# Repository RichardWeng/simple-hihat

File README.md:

# simple-hihat
 Simple eurorack hihat module

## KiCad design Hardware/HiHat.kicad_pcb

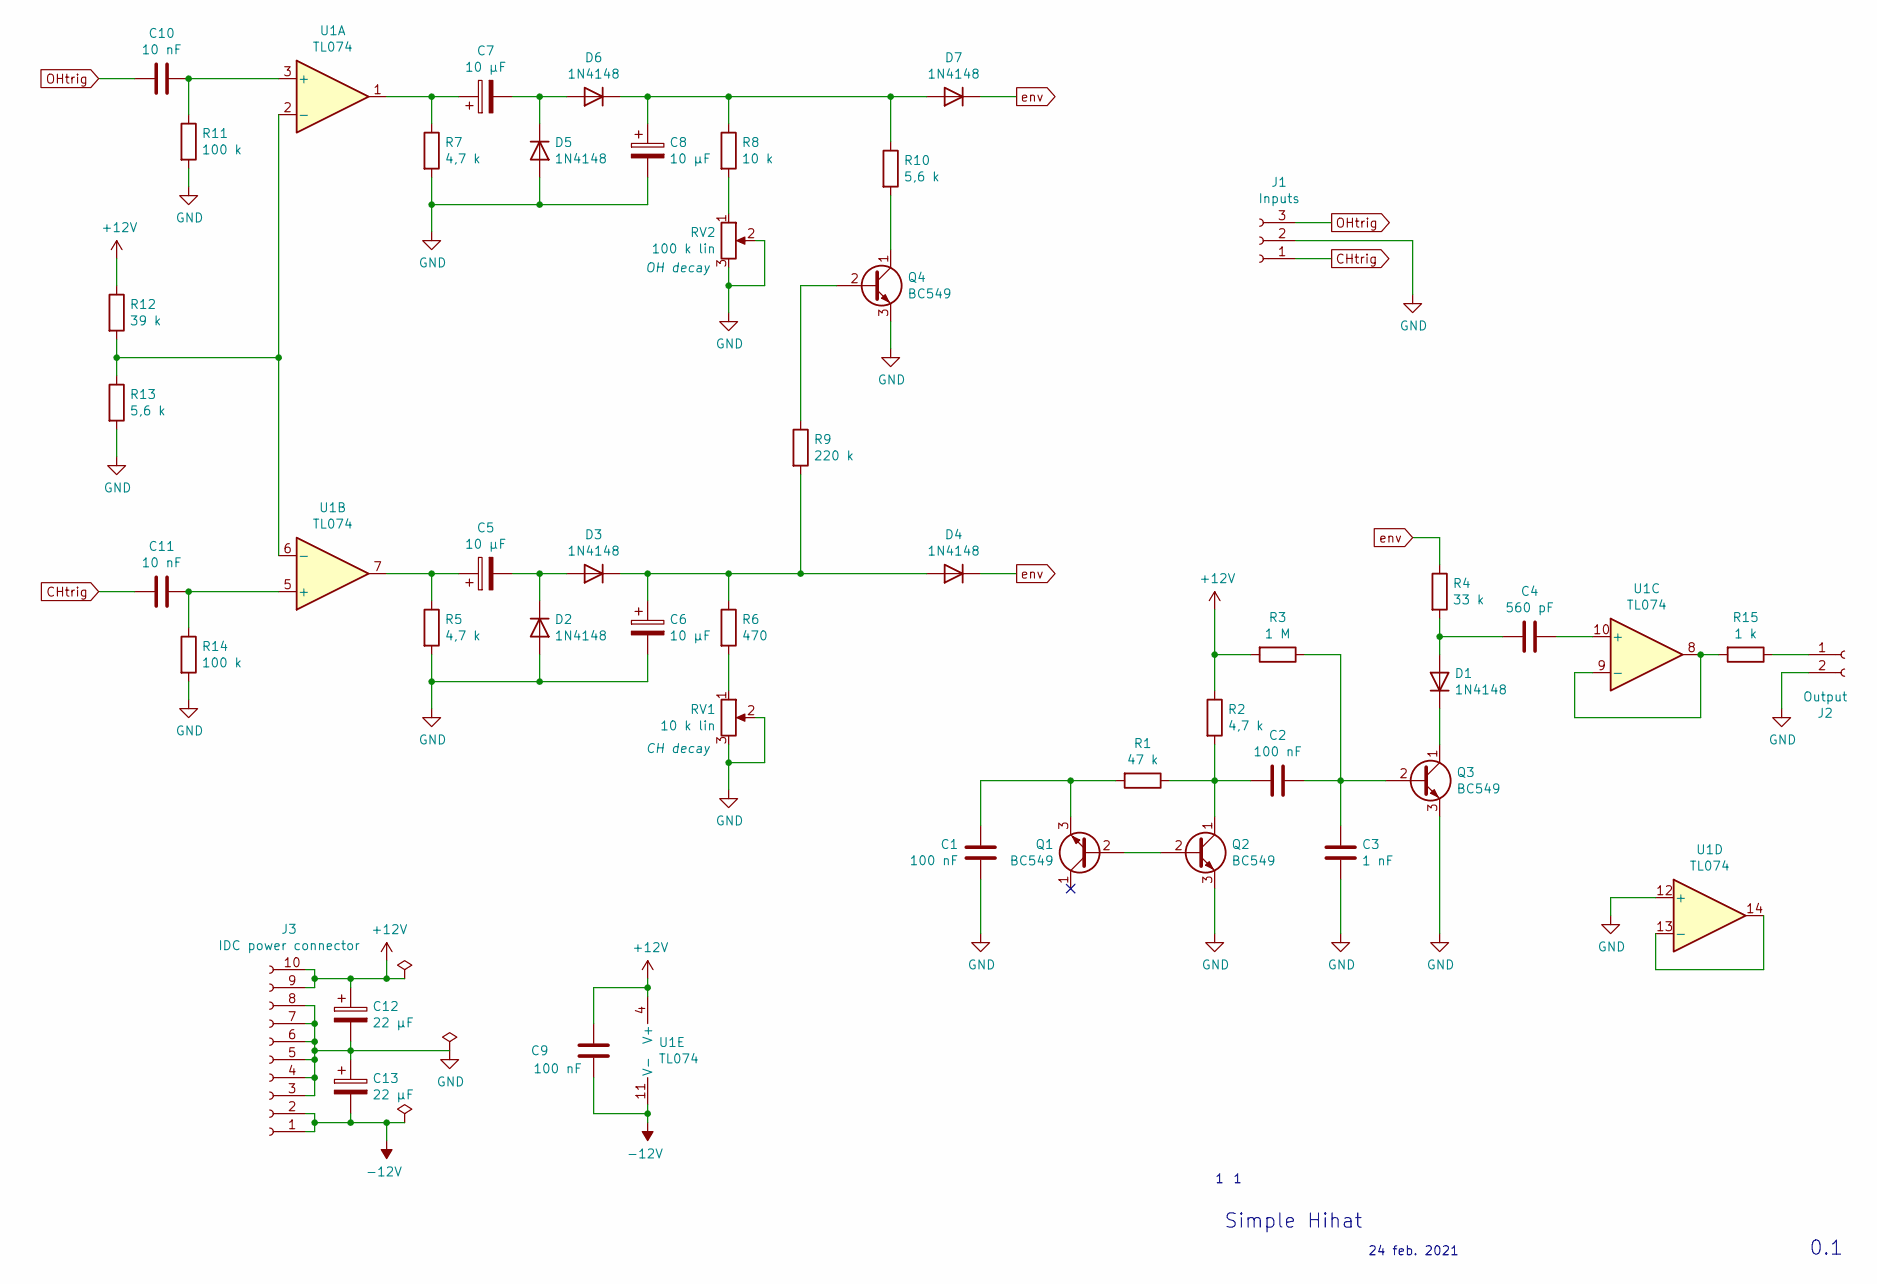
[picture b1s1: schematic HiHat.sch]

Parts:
C1, C2: 100 nF; C_Rect_L7.2mm_W5.5mm_P5.00mm_FKS2_FKP2_MKS2_MKP2
C3: 1 nF; C_Rect_L7.2mm_W2.5mm_P5.00mm_FKS2_FKP2_MKS2_MKP2
C4: 560 pF; C_Disc_D4.3mm_W1.9mm_P5.00mm
C5, C6, C7, C8: 10 µF; CP_Radial_D6.3mm_P2.50mm
C9: 100 nF; C_Rect_L7.2mm_W2.5mm_P5.00mm_FKS2_FKP2_MKS2_MKP2
C10, C11: 10 nF; C_Rect_L7.2mm_W5.5mm_P5.00mm_FKS2_FKP2_MKS2_MKP2
C12, C13: 22 µF; CP_Radial_D6.3mm_P2.50mm
D1, D2, D3, D4, D5, D6, D7: 1N4148; D_DO-35_SOD27_P10.16mm_Horizontal
J1: Inputs; JST_EH_B3B-EH-A_1x03_P2.50mm_Vertical
J2: Output; JST_EH_B2B-EH-A_1x02_P2.50mm_Vertical
J3: IDC power connector; IDC-Header_2x05_P2.54mm_Vertical
Q1, Q2, Q3, Q4: BC549; TO-92_Inline_Wide
R1: 47 k; R_Axial_DIN0207_L6.3mm_D2.5mm_P10.16mm_Horizontal
R2, R5, R7: 4,7 k; R_Axial_DIN0207_L6.3mm_D2.5mm_P10.16mm_Horizontal
R3: 1 M; R_Axial_DIN0207_L6.3mm_D2.5mm_P10.16mm_Horizontal
R4: 33 k; R_Axial_DIN0207_L6.3mm_D2.5mm_P10.16mm_Horizontal
R6: 470; R_Axial_DIN0207_L6.3mm_D2.5mm_P10.16mm_Horizontal
R8: 10 k; R_Axial_DIN0207_L6.3mm_D2.5mm_P10.16mm_Horizontal
R9: 220 k; R_Axial_DIN0207_L6.3mm_D2.5mm_P10.16mm_Horizontal
R10, R13: 5,6 k; R_Axial_DIN0207_L6.3mm_D2.5mm_P10.16mm_Horizontal
R11, R14: 100 k; R_Axial_DIN0207_L6.3mm_D2.5mm_P10.16mm_Horizontal
R12: 39 k; R_Axial_DIN0207_L6.3mm_D2.5mm_P10.16mm_Horizontal
R15: 1 k; R_Axial_DIN0207_L6.3mm_D2.5mm_P10.16mm_Horizontal
RV1: 10 k lin; Potentiometer_Alps_RK09Y11_Single_Horizontal
RV2: 100 k lin; Potentiometer_Alps_RK09Y11_Single_Horizontal
U1: TL074; DIP-14_W7.62mm_Socket_LongPads

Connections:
+12V: C9.1, C12.1, J3.9, J3.10, R2.1, R3.2, R12.1, U1.4 (V+)
-12V: C9.2, C13.2, J3.1, J3.2, U1.11 (V-)
CHtrig: C11.2, J1.1
GND: C1.2, C3.2, C6.2, C8.2, C12.2, C13.1, D2.2 (A), D5.2 (A), J1.2, J2.2, J3.3, J3.4, J3.5, J3.6, J3.7, J3.8, Q2.3 (E), Q3.3 (E), Q4.3 (E), R5.2, R7.2, R11.2, R13.2, R14.2, RV1.2, RV1.3, RV2.2, RV2.3, U1.12 (+)
unnamed: C1.1, Q1.3 (E), R1.2
unnamed: C2.1, C3.1, Q3.2 (B), R3.1
unnamed: C2.2, Q2.1 (C), R1.1, R2.2
unnamed: C4.1, D1.2 (A), R4.2
unnamed: C4.2, U1.10 (+)
unnamed: C5.1, R5.1, U1.7
unnamed: C5.2, D2.1 (K), D3.2 (A)
unnamed: C6.1, D3.1 (K), D4.2 (A), R6.1, R9.2
unnamed: C7.1, R7.1, U1.1
unnamed: C7.2, D5.1 (K), D6.2 (A)
unnamed: C8.1, D6.1 (K), D7.2 (A), R8.1, R10.1
unnamed: C10.1, R11.1, U1.3 (+)
unnamed: C11.1, R14.1, U1.5 (+)
unnamed: D1.1 (K), Q3.1 (C)
unnamed: J2.1, R15.1
unnamed: Q1.2 (B), Q2.2 (B)
unnamed: Q4.1 (C), R10.2
unnamed: Q4.2 (B), R9.1
unnamed: R6.2, RV1.1
unnamed: R8.2, RV2.1
unnamed: R12.2, R13.1, U1.2 (-), U1.6 (-)
unnamed: R15.2, U1.8, U1.9 (-)
unnamed: U1.13 (-), U1.14
OHtrig: C10.2, J1.3
env: D4.1 (K), D7.1 (K), R4.1

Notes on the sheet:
Simple Hihat
24 feb. 2021
0.1

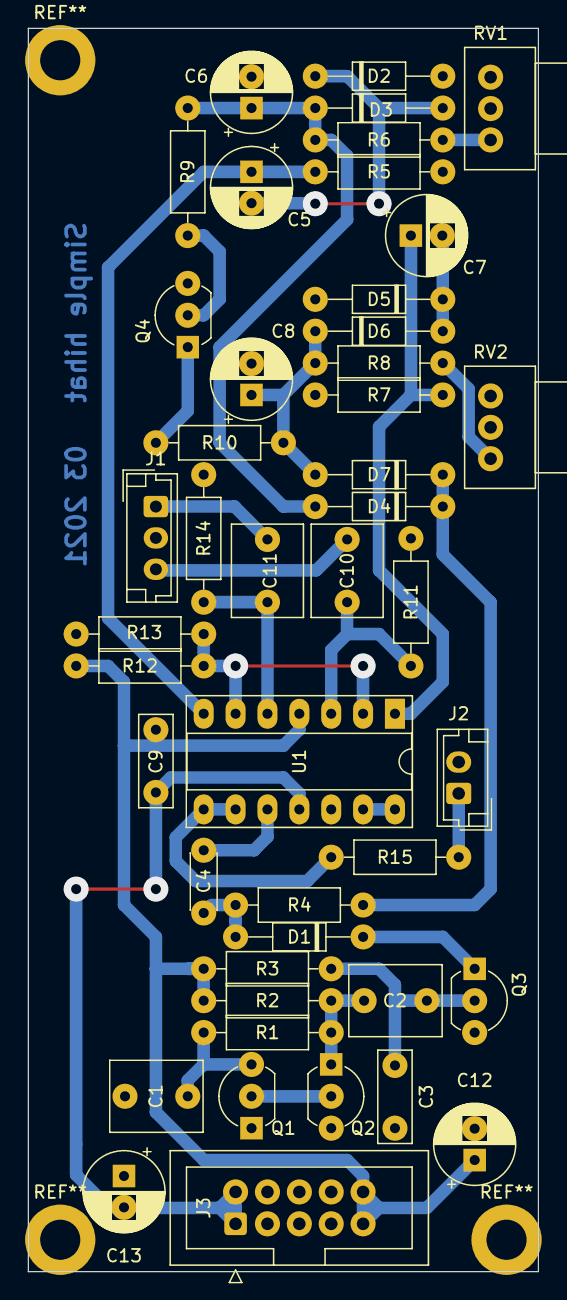
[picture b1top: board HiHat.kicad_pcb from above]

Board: 2 copper layers, 40.6 x 99.1 mm, 45 parts (0 on the bottom side), 29 nets.

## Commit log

2021-02-24 Added input conditioners and output buffer
2021-02-25 Completed sch info
2021-02-25 PCB first draft
2021-03-01 PCB routing
